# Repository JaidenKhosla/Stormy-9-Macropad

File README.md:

# Stormy 9 - A Macropad Designed for Simplicity
## *In today's age of mechanical keyboards, people value simplicity and customizability. The Stormy 9 allows this by having up to 16 programmable buttons, a knob to adjust volume and brightness, and an OLED display that shows off your WPM and a cute picture of my cat (non-negotiable).*

### \* *The case is mounted from the bottom. In my current setup, a top mounted case would look bad (not saying top mounted cases look ugly or anything, it just wouldn't work for my personal setup).*

## Personal Use:
####  A bit off topic, but I'm probably going to use this macropad for additional keybinds for video games (probably CS2 with their buy menu). Also, I've always desired to adjust my volume and brightness with ease as my current keyboard doesn't have a knob.

## PCB Schematic (Made with KICAD)

#### I learned PCB schematics through ScottoKeeb's tutorial (https://youtu.be/8WXpGTIbxlQ?si=Y5YSVLcabkqrECWy). It was genuinely super helpful and I would've spent so many more hours without it.

## PCB Layout

## 3D Model of The Stormy 9
#### For context, I tried using Fusion-360 to design the case (like any normal person would). However, Fusion-360 refused to import STEP and STL files (I wanted to import the 3D model of my PCB for rendering and ease of modeling), forcing me to voluntarily choose Blender. Contrary to popular belief, Blender was actually super easy and useful to model the case. For anyone planning to design their case in Blender, please google what non-manifold edges are before starting (it will save you so much time in the future). To convert the models to STEP files, I utilized the open-sourced software, FreeCAD.

## 3D render of the backside of the Stormy 9

## Firmware
### For the firmware, I utilized the open-source project, QMK. I found this to be a lot better than KMK as it's still officially maintained and gave developers a lot more granular control. It also forces you to code in C rather than Python (Take that as a bonus or a burden). 

# __Materials Needed:__
### * 1 Seeed XIAO RP2040 Microcontroller
### * 9 1N4148 Through-Hole Diodes
### * 9 MX-style Mechanical Switches
### * 1 EC11 Rotary Encoder
### * 1 0.91" 128X32 OLED Display
### * 9 Blank DSA Keycaps
### * 4 M3x16mm Screws
### * 4 M3x5x4mm Heatset Inserts
### * Sanity

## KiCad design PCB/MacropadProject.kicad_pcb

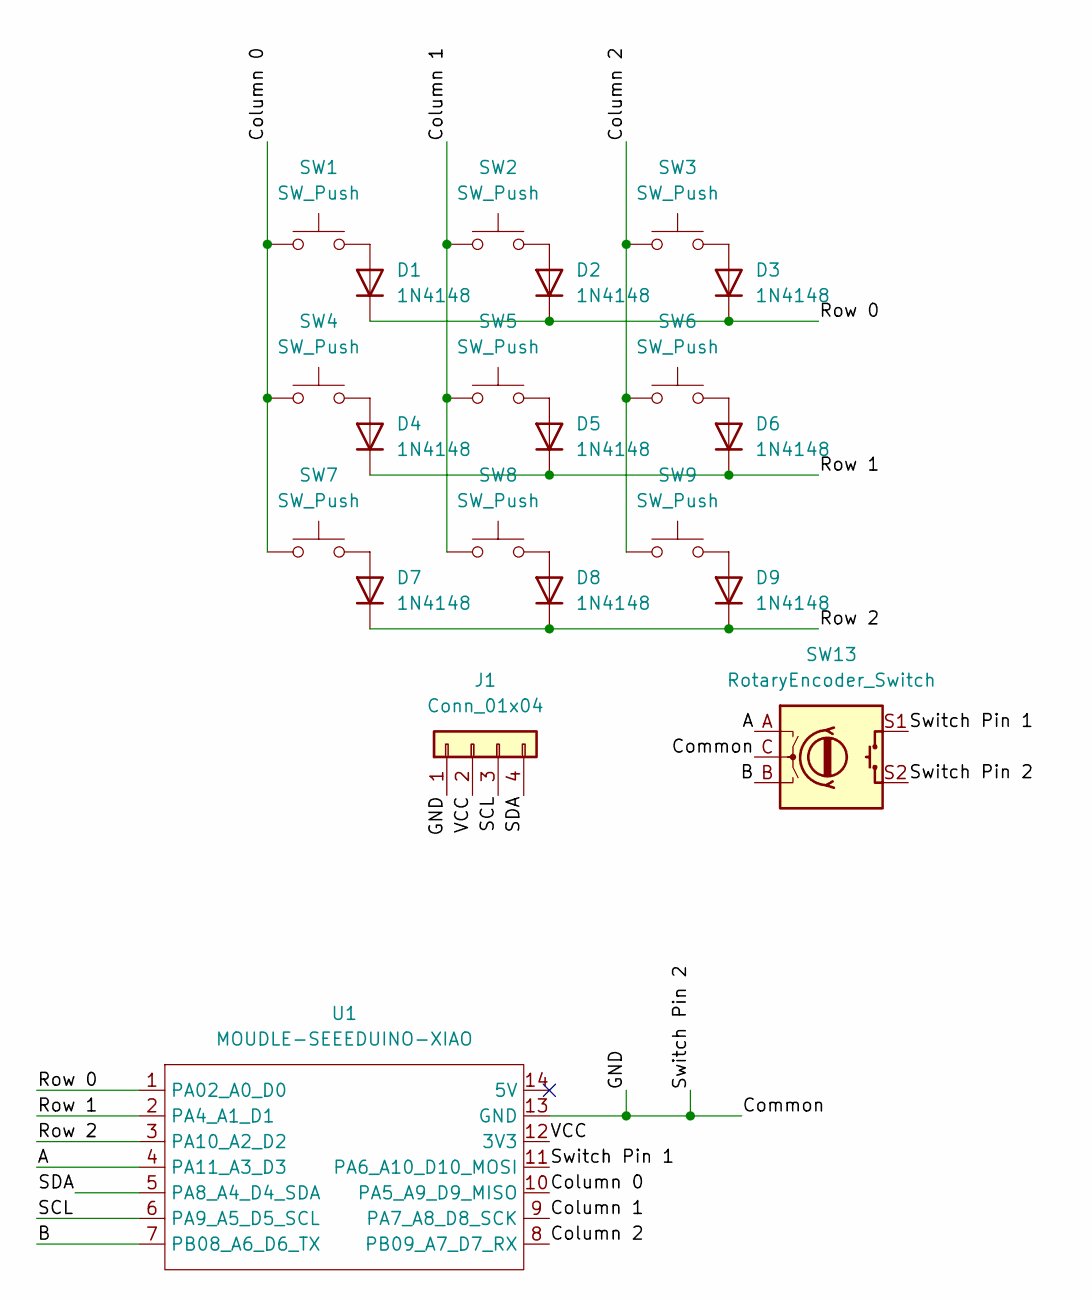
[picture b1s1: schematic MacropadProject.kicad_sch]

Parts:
D1, D2, D3, D4, D5, D6, D7, D8, D9: 1N4148; D_DO-35_SOD27_P7.62mm_Horizontal
J1: Conn_01x04; SSD1306-0.91-OLED-4pin-128x32
SW1, SW2, SW3, SW4, SW5, SW6, SW7, SW8, SW9: SW_Push; SW_Cherry_MX_1.00u_PCB
SW13: RotaryEncoder_Switch; RotaryEncoder_Alps_EC11E-Switch_Vertical_H20mm
U1: MOUDLE-SEEEDUINO-XIAO; XIAO-Generic-Hybrid-14P-2.54-21X17.8MM

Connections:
/A: SW13.A, U1.4 (PA11_A3_D3)
/B: SW13.B, U1.7 (PB08_A6_D6_TX)
/Column 0: SW1.1, SW4.1, SW7.1, U1.10 (PA5_A9_D9_MISO)
/Column 1: SW2.1, SW5.1, SW8.1, U1.9 (PA7_A8_D8_SCK)
/Column 2: SW3.1, SW6.1, SW9.1, U1.8 (PB09_A7_D7_RX)
/Common: J1.1, SW13.C, SW13.S2, U1.13 (GND)
/Row 0: D1.1 (K), D2.1 (K), D3.1 (K), U1.1 (PA02_A0_D0)
/Row 1: D4.1 (K), D5.1 (K), D6.1 (K), U1.2 (PA4_A1_D1)
/Row 2: D7.1 (K), D8.1 (K), D9.1 (K), U1.3 (PA10_A2_D2)
/SCL: J1.3, U1.6 (PA9_A5_D5_SCL)
/SDA: J1.4, U1.5 (PA8_A4_D4_SDA)
/Switch Pin 1: SW13.S1, U1.11 (PA6_A10_D10_MOSI)
/VCC: J1.2, U1.12 (3V3)
unnamed: D1.2 (A), SW1.2
unnamed: D2.2 (A), SW2.2
unnamed: D3.2 (A), SW3.2
unnamed: D4.2 (A), SW4.2
unnamed: D5.2 (A), SW5.2
unnamed: D6.2 (A), SW6.2
unnamed: D7.2 (A), SW7.2
unnamed: D8.2 (A), SW8.2
unnamed: D9.2 (A), SW9.2

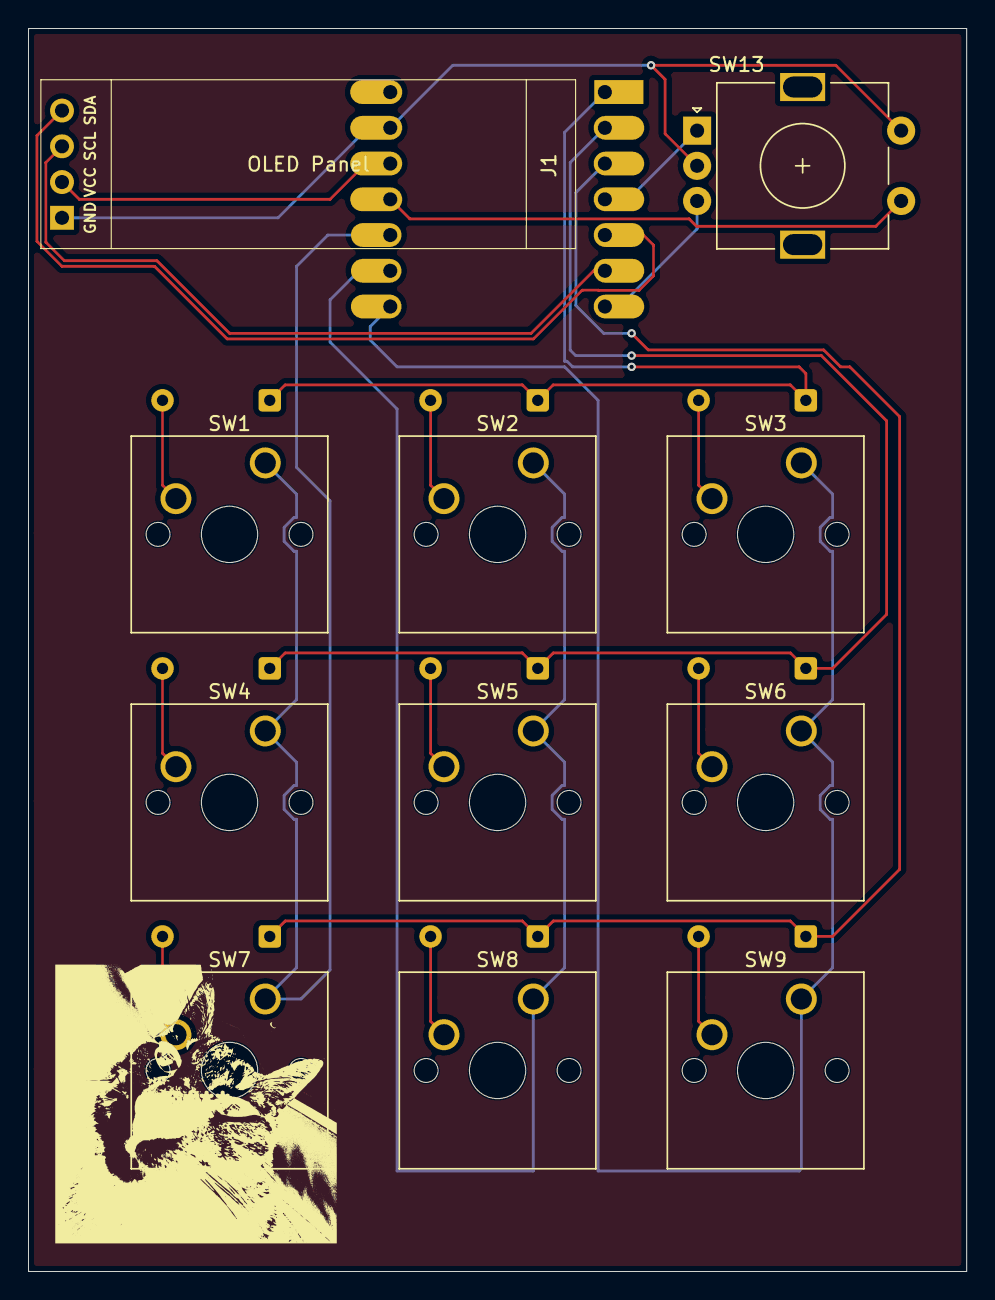
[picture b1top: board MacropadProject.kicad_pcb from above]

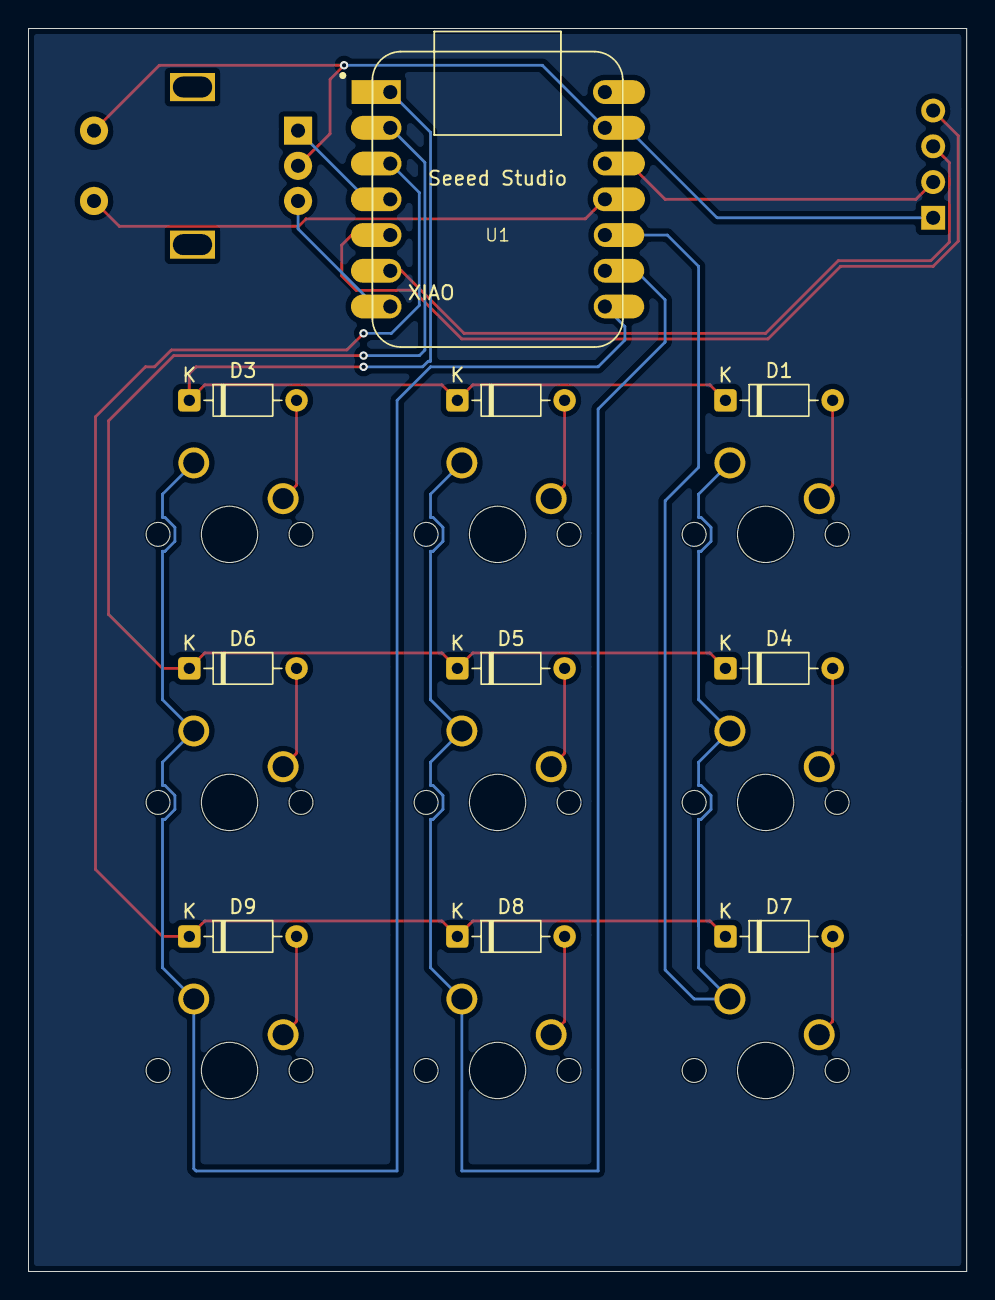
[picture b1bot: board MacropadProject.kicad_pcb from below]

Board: 2 copper layers, 66.7 x 88.3 mm, 21 parts (10 on the bottom side), 22 nets.

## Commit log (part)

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2026-06-14 added to README
